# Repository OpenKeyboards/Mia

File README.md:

# Mia
122 key keyboard PCB with usb spi uart i2c

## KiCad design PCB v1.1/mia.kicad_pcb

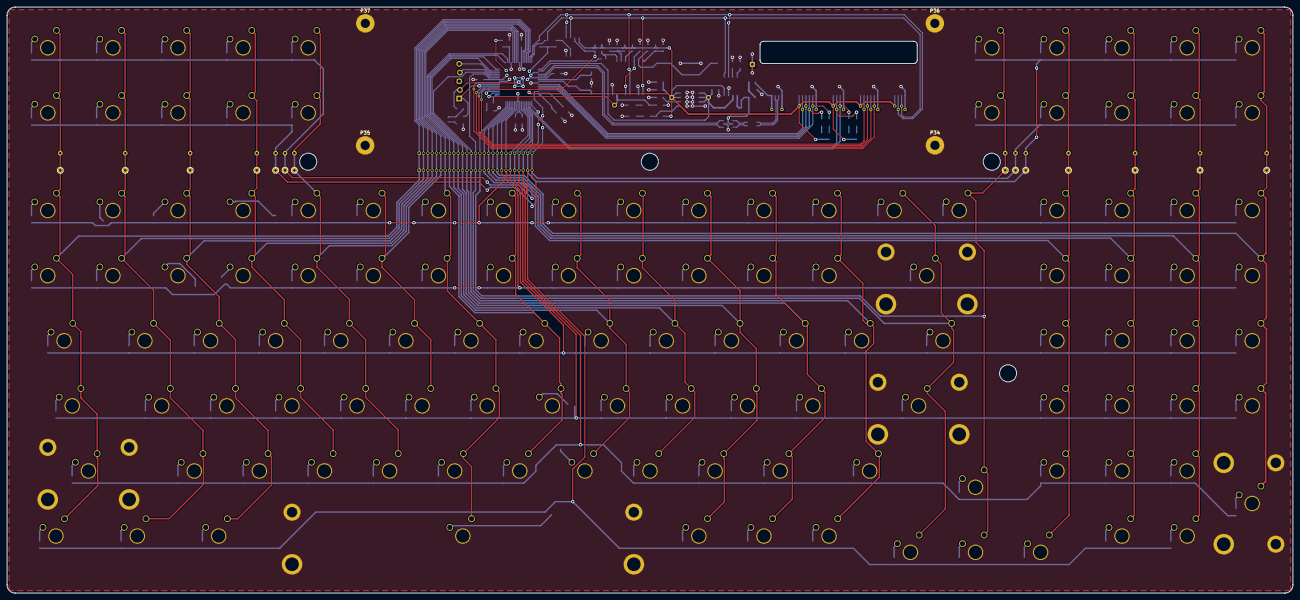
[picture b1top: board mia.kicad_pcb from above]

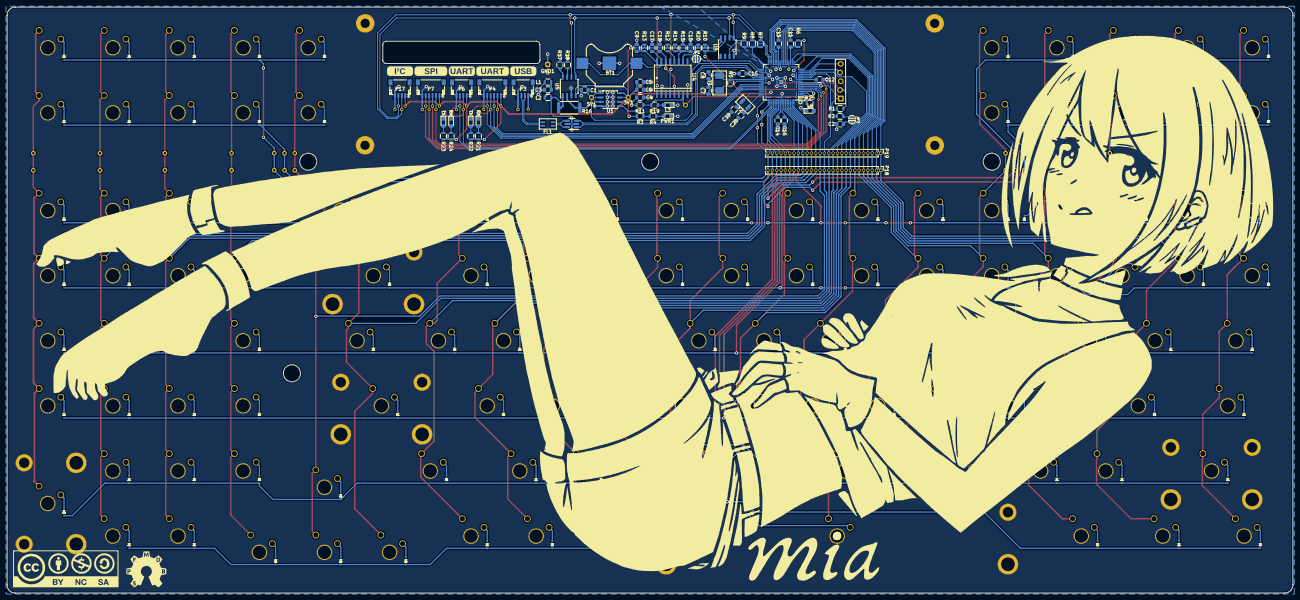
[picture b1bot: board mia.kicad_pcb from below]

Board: 2 copper layers, 376.2 x 171.5 mm, 353 parts (199 on the bottom side), 205 nets.

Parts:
3V3: 3.3V; Measurement_Point_Round-TH_Small
5V1: 5V; Measurement_Point_Round-TH_Small
BT1: Battery_Cell; Keystone_3000_1x12mm-CoinCell
C1, C5: 2.2uF; C_0805
C2, C4, C6, C9, C10, C11, C12, C13, C15, C16, C17, C18: 0.1uF; C_0805
C3: 630nF 16V; C_0805
C7, C8: 18pF; C_0805
C14: 10uF; C_0805
C19, C20: 12.5pF; C_0805
D1, D2, D3, D4, D5, D6, D7, D8, D9, D10, D11, D12, D13, D14, D15, D16, D17, D18, D19, D20, D21, D22, D23, D24, D25, D26, D27, D28, D29, D30, D31, D32, D33, D34, D35, D36, D37, D38, D39, D40, D41, D42, D43, D44, D45, D46, D47, D48, D49, D50, D51, D52, D53, D54, D55, D56, D57, D58, D59, D60, D61, D62, D63, D64, D65, D66, D67, D68, D69, D70, D71, D72, D73, D74, D75, D76, D77, D78, D79, D80, D81, D82, D83, D84, D85, D86, D87, D88, D89, D90, D91, D92, D93, D94, D95, D96, D97, D98, D99, D100, D101, D102, D103, D104, D105, D106, D107, D108, D109, D110, D111, D112, D113, D114, D116, D117, D118, D119, D120, D121, D122: D; D_SOD-323-NOMASK
D127: TVSDiodeArray; SOT-23-6_Handsoldering
FL1: EMI_Filter_LL; USBChoke
GND1: GND; Measurement_Point_Square-TH_Small
JP1, JP3: Jumper_NO_Small; SOLDER-JUMPER_1-WAY
L1, L2: 1.5A 600Ohms@100Mhz; L_0805
L3: PPS; LED_0805
L8: BL; LED_0805
P1, P8, P9, P10, P11, P12, P13, P14, P15, P16: CONN_01X01; PCBSTAB
P2: ISCP HEADER; ISCP_Header
P3: CONN_01X06; JST4x1.00mm_AngledUSB
P4, P7: CONN_01X06; JST_SH_6x1_Angled
P5: ViaPattern; spiheader
P6, P17: CONN_01X04; JST4x1.00mm_Angled
P18, P19: CONN_01X27; Pin_Header_Straight_1x27_Pitch1.27mm
P20, P21, P22, P23, P24, P25, P26, P27, P28, P29, P30, P31, P32, P33: CONN_01X01; throughholelink
P34, P35, P36, P37: CONN_01X01; MountingHole_2.7mm_M2.5_Pad
P38, P39, P40, P41: CONN_01X01; m25MountingClearance
PWR1: PWR; LED_0805
R1, R11, R12, R14, R15, R17, R18, R20: 10k; R_0805
R2: 1k; R_0805
R3: 200k; R_0805
R4: R; R_0805
R5: 1M; R_0805
R6: 10R; R_0805
R7, R8: 4.7k; R_0805
R9, R10: 100k; R_0805
R13, R19, R21, R22, R23, R24, R25: 330R; R_0805
R16: SENSE; R_2512
RX: RX; LED_0805
RX#2: RX; LED_0805
S1, S2, S3, S4, S5, S6, S7, S8, S9, S10, S11, S12, S13, S14, S15, S16, S17, S18, S19, S20, S21, S22, S23, S24, S25, S26, S27, S28, S29, S30, S31, S32, S33, S34, S35, S36, S37, S38, S39, S40, S41, S42, S43, S44, S45, S46, S47, S48, S49, S50, S51, S52, S53, S54, S55, S56, S57, S58, S59, S60, S61, S62, S63, S64, S65, S66, S67, S68, S69, S70, S71, S72, S73, S74, S75, S76, S77, S78, S79, S80, S81, S82, S83, S84, S85, S86, S87, S88, S89, S90, S91, S92, S93, S94, S95, S96, S97, S98, S99, S100, S101, S102, S103, S104, S105, S106, S107, S108, S109, S110, S111, S112, S113, S114, S116, S117, S118, S119, S120, S121, S122: SW; SW_SOCKET_COMBINED_T
TP1: TEST; Measurement_Point_Round-TH_Small
TX: TX; LED_0805
TX#2: TX; LED_0805
U1: MCP1727; SOIC-8_3.9x4.9mm_Pitch1.27mm
U2: PIC32MX470F512H
U3: M24M02-DR; SOIC-8_3.9x4.9mm_Pitch1.27mm
U4: pcf2127t; NXP-SO16
U5: INA219; SOIC-8_3.9x4.9mm_Pitch1.27mm
Y1: 20Mhz; OSCAB7
Y2: 32.768Mhz; ECX-327-CDX-1293

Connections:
+3V3: 3V3.1, C5.1, C6.1, C12.1, C13.1, C15.2, C16.1, P2.2, P4.1, P6.1, P7.1, P17.1, R1.2, R3.1, R6.2, R7.2, R8.2, R9.1, R10.2, R11.2, R12.1, R13.1, R14.1, R20.2, R21.1, R22.1, R23.1, R24.1, U1.7, U1.8, U2.10, U2.26, U2.35, U2.38, U2.57, U3.8, U5.4
+5V: 5V1.1, C1.1, R16.2, U1.1, U1.2, U1.3, U2.34, U5.2
/1D+: D127.6, FL1.2
/1D-: D127.4, FL1.3
/2D+: FL1.1, P3.3
/2D-: FL1.4, P3.2
BBS: C18.1, U4.5, U4.14
COL00: P18.1, P19.1, P20.1, S1.2, S2.2, S3.2, S4.2, S5.2, S6.2, S7.2, S8.2, U2.30
COL01: P18.2, P19.2, P21.1, S9.2, S10.2, S11.2, S12.2, S13.2, S14.2, S15.2, S16.2, U2.29
COL02: P18.3, P19.3, P22.1, S17.2, S18.2, S19.2, S20.2, S21.2, S22.2, S23.2, S24.2, U2.28
COL03: P18.4, P19.4, P23.1, S25.2, S26.2, S27.2, S28.2, S29.2, S30.2, S31.2, U2.27
COL04: P18.5, P19.5, P24.1, S32.2, S33.2, S34.2, S35.2, S36.2, S37.2, S38.2, U2.24
COL05: P18.6, P19.6, S39.2, S40.2, S41.2, S42.2, U2.23
COL06: P18.7, P19.7, S43.2, S44.2, S45.2, S46.2, S47.2, S48.2, U2.22
COL07: P18.8, P19.8, S49.2, S50.2, S51.2, S52.2, S53.2, U2.21
COL08: P18.9, P19.9, S54.2, S55.2, S56.2, S57.2, S58.2, U2.18
COL09: P18.10, P19.10, S59.2, S60.2, S61.2, S62.2, S63.2, U2.17
COL10: P18.11, P19.11, S64.2, S65.2, S66.2, S67.2, S68.2, S69.2, U2.16
COL11: P18.12, P19.12, S70.2, S71.2, S72.2, S73.2, S74.2, S75.2, U2.15
COL12: P18.13, P19.13, S76.2, S77.2, S78.2, S79.2, S80.2, U2.12
COL13: P18.14, P19.14, S81.2, S82.2, S83.2, S84.2, S85.2, U2.11
COL14: P18.15, P19.15, P25.1, S86.2, S87.2, S88.2, S89.2, S90.2, U2.64
COL15: P18.16, P19.16, P26.1, S91.2, S92.2, S93.2, S94.2, S95.2, S96.2, S97.2, S98.2, U2.63
COL16: P18.17, P19.17, P27.1, S99.2, S100.2, S101.2, S102.2, S103.2, S104.2, S105.2, S106.2, U2.62
COL17: P18.18, P19.18, P28.1, S107.2, S108.2, S109.2, S110.2, S111.2, S112.2, S113.2, S114.2, U2.61
COL18: P18.19, P19.19, P29.1, S116.2, S117.2, S118.2, S119.2, S120.2, S121.2, S122.2, U2.60
EEPROM_WRITE_CONTROL: R10.1, U2.3, U3.7
GND: BT1.2, C1.2, C2.2, C3.2, C4.2, C5.2, C6.2, C7.2, C8.2, C9.2, C10.2, C11.2, C12.2, C13.2, C14.2, C15.1, C16.2, C17.2, C18.2, C19.2, C20.2, D127.2, GND1.1, L3.1, L8.1, P1.1, P2.3, P3.4, P4.6, P6.4, P7.6, P8.1, P9.1, P10.1, P11.1, P12.1, P13.1, P14.1, P15.1, P16.1, P17.4, P34.1, P35.1, P36.1, P37.1, PWR1.1, R15.1, R17.1, R18.1, S1.3, S2.3, S3.3, S4.3, S5.3, S6.3, S7.3, S8.3, S9.3, S10.3, S11.3, S12.3, S13.3, S14.3, S15.3, S16.3, S17.3, S18.3, S19.3, S20.3, S21.3, S22.3, S23.3, S24.3, S25.3, S26.3, S27.3, S28.3, S29.3, S30.3, S31.3, S32.3, S33.3, S34.3, S35.3, S36.3, S37.3, S38.3, S39.3, S40.3, S41.3, S42.3, S43.3, S44.3, S45.3, S46.3, S47.3, S48.3, S49.3, S50.3, S51.3, S52.3, S53.3, S54.3, S55.3, S56.3, S57.3, S58.3, S59.3, S60.3, S61.3, S62.3, S63.3, S64.3, S65.3, S66.3, S67.3, S68.3, S69.3, S70.3, S71.3, S72.3, S73.3, S74.3, S75.3, S76.3, S77.3, S78.3, S79.3, S80.3, S81.3, S82.3, S83.3, S84.3, S85.3, S86.3, S87.3, S88.3, S89.3, S90.3, S91.3, S92.3, S93.3, S94.3, S95.3, S96.3, S97.3, S98.3, S99.3, S100.3, S101.3, S102.3, S103.3, S104.3, S105.3, S106.3, S107.3, S108.3, S109.3, S110.3, S111.3, S112.3, S113.3, S114.3, S116.3, S117.3, S118.3, S119.3, S120.3, S121.3, S122.3, U1.4, U2.9, U2.20, U2.25, U2.41, U3.4, U4.2, U4.8, U5.3
MCLR: P2.1, R2.1, U2.7
unnamed: BT1.1, C17.1, U4.15
unnamed: C2.1, JP3.2
unnamed: C3.1, L1.1, L2.2
unnamed: C4.1, U1.6
unnamed: C9.1, R13.2, U4.16
unnamed: C10.1, R14.2, R15.2, U4.11
unnamed: C11.1, R6.1, U2.19
unnamed: C14.1, U2.56
unnamed: D1.1, S1.1
unnamed: D2.1, S2.1
unnamed: D3.1, S3.1
unnamed: D4.1, S4.1
unnamed: D5.1, S5.1
unnamed: D6.1, S6.1
unnamed: D7.1, S7.1
unnamed: D8.1, S8.1
unnamed: D9.1, S9.1
unnamed: D10.1, S10.1
unnamed: D11.1, S11.1
unnamed: D12.1, S12.1
unnamed: D13.1, S13.1
unnamed: D14.1, S14.1
unnamed: D15.1, S15.1
unnamed: D16.1, S16.1
unnamed: D17.1, S17.1
unnamed: D18.1, S18.1
unnamed: D19.1, S19.1
unnamed: D20.1, S20.1
unnamed: D21.1, S21.1
unnamed: D22.1, S22.1
unnamed: D23.1, S23.1
unnamed: D24.1, S24.1
unnamed: D25.1, S25.1
unnamed: D26.1, S26.1
unnamed: D27.1, S27.1
unnamed: D28.1, S28.1
unnamed: D29.1, S29.1
unnamed: D30.1, S30.1
unnamed: D31.1, S31.1
unnamed: D32.1, S32.1
unnamed: D33.1, S33.1
unnamed: D34.1, S34.1
unnamed: D35.1, S35.1
unnamed: D36.1, S36.1
unnamed: D37.1, S37.1
unnamed: D38.1, S38.1
unnamed: D39.1, S39.1
unnamed: D40.1, S40.1
unnamed: D41.1, S41.1
unnamed: D42.1, S42.1
unnamed: D43.1, S43.1
unnamed: D44.1, S44.1
unnamed: D45.1, S45.1
unnamed: D46.1, S46.1
unnamed: D47.1, S47.1
unnamed: D48.1, S48.1
unnamed: D49.1, S49.1
unnamed: D50.1, S50.1
unnamed: D51.1, S51.1
unnamed: D52.1, S52.1
unnamed: D53.1, S53.1
unnamed: D54.1, S54.1
unnamed: D55.1, S55.1
unnamed: D56.1, S56.1
unnamed: D57.1, S57.1
unnamed: D58.1, S58.1
unnamed: D59.1, S59.1
unnamed: D60.1, S60.1
unnamed: D61.1, S61.1
unnamed: D62.1, S62.1
unnamed: D63.1, S63.1
unnamed: D64.1, S64.1
unnamed: D65.1, S65.1
unnamed: D66.1, S66.1
unnamed: D67.1, S67.1
unnamed: D68.1, S68.1
unnamed: D69.1, S69.1
unnamed: D70.1, S70.1
unnamed: D71.1, S71.1
unnamed: D72.1, S72.1
unnamed: D73.1, S73.1
unnamed: D74.1, S74.1
unnamed: D75.1, S75.1
unnamed: D76.1, S76.1
unnamed: D77.1, S77.1
unnamed: D78.1, S78.1
unnamed: D79.1, S79.1
unnamed: D80.1, S80.1
unnamed: D81.1, S81.1
unnamed: D82.1, S82.1
unnamed: D83.1, S83.1
unnamed: D84.1, S84.1
unnamed: D85.1, S85.1
unnamed: D86.1, S86.1
unnamed: D87.1, S87.1
unnamed: D88.1, S88.1
unnamed: D89.1, S89.1
unnamed: D90.1, S90.1
unnamed: D91.1, S91.1
unnamed: D92.1, S92.1
unnamed: D93.1, S93.1
unnamed: D94.1, S94.1
unnamed: D95.1, S95.1
unnamed: D96.1, S96.1
unnamed: D97.1, S97.1
unnamed: D98.1, S98.1
unnamed: D99.1, S99.1
unnamed: D100.1, S100.1
unnamed: D101.1, S101.1
unnamed: D102.1, S102.1
unnamed: D103.1, S103.1
unnamed: D104.1, S104.1
unnamed: D105.1, S105.1
unnamed: D106.1, S106.1
unnamed: D107.1, S107.1
unnamed: D108.1, S108.1
unnamed: D109.1, S109.1
unnamed: D110.1, S110.1
unnamed: D111.1, S111.1
unnamed: D112.1, S112.1
unnamed: D113.1, S113.1
unnamed: D114.1, S114.1
unnamed: D116.1, S116.1
unnamed: D117.1, S117.1
unnamed: D118.1, S118.1
unnamed: D119.1, S119.1
unnamed: D120.1, S120.1
unnamed: D121.1, S121.1
unnamed: D122.1, S122.1
unnamed: D127.5, L2.1, R16.1, U5.1
unnamed: JP1.2, R20.1, U4.10
unnamed: JP3.1, R1.1, R2.2
unnamed: L1.2, P3.1
unnamed: L3.2, R19.2
unnamed: R21.2, RX.2
unnamed: R22.2, TX.2
unnamed: R23.2, TX#2.2
unnamed: R24.2, RX#2.2
unnamed: L8.2, R25.2
unnamed: PWR1.2, R4.1
unnamed: R3.2, R4.2, U1.5
unnamed: R9.2, U3.3
unnamed: R12.2, U4.12
unnamed: R17.2, U5.8
unnamed: R18.2, U5.7
unnamed: R25.1, U2.1
OSC1: C8.1, R5.2, U2.39, Y1.1
OSC2: C7.1, R5.1, U2.40, Y1.2
PGEC3: P2.5, U2.14
PGED3: P2.4, U2.13
POWERFAIL: JP1.1, U2.33
ROW0: D1.2, D9.2, D17.2, D25.2, D32.2, D86.2, D91.2, D99.2, D107.2, D116.2, P18.26, P19.26, P30.1, P32.1, U2.49
ROW1: D2.2, D10.2, D18.2, D26.2, D33.2, D87.2, D92.2, D100.2, D108.2, D117.2, P18.27, P19.27, P31.1, P33.1, U2.46
ROW2: D3.2, D11.2, D19.2, D27.2, D34.2, D39.2, D43.2, D49.2, D54.2, D59.2, D64.2, D70.2, D76.2, D81.2, D88.2, D93.2, D101.2, D109.2, D118.2, P18.20, P19.20, U2.59
ROW3: D4.2, D12.2, D20.2, D28.2, D35.2, D40.2, D44.2, D50.2, D55.2, D60.2, D65.2, D71.2, D77.2, D82.2, D94.2, D102.2, D110.2, D119.2, P18.21, P19.21, U2.58
ROW4: D5.2, D13.2, D21.2, D29.2, D36.2, D41.2, D45.2, D51.2, D56.2, D61.2, D66.2, D72.2, D78.2, D83.2, D95.2, D103.2, D111.2, D120.2, P18.22, P19.22, U2.55
ROW5: D6.2, D14.2, D22.2, D30.2, D37.2, D42.2, D46.2, D52.2, D57.2, D62.2, D67.2, D73.2, D84.2, D96.2, D104.2, D112.2, D121.2, P18.23, P19.23, U2.54
ROW6: D7.2, D15.2, D23.2, D31.2, D38.2, D47.2, D53.2, D58.2, D63.2, D68.2, D74.2, D79.2, D89.2, D97.2, D105.2, D113.2, D122.2, P18.24, P19.24, U2.53
ROW7: D8.2, D16.2, D24.2, D48.2, D69.2, D75.2, D80.2, D85.2, D90.2, D98.2, D106.2, D114.2, P18.25, P19.25, U2.52
RTC_CLK: R11.1, R19.1, TP1.1, U2.2, U4.7
SCL2: P17.3, R8.1, U2.32, U3.6, U4.1, U5.5
SDA2: P17.2, R7.1, U2.31, U3.5, U4.4, U5.6
SOSCI: C19.1, U2.47, Y2.2
SOSCO: C20.1, U2.48, Y2.1
SPI2-CLK: P5.1, P7.2, U2.4
SPI2-CS: P5.4, P7.5, U2.8
SPI2-MISO: P5.2, P7.3, U2.5
SPI2-MOSI: P5.3, P7.4, U2.6
UART1CTS: P4.3, U2.43
UART1RTS: P4.2, U2.42
UART1RX: P4.4, RX.1, U2.44
UART1TX: P4.5, TX.1, U2.45
UART3RX: P6.3, RX#2.1, U2.51
UART3TX: P6.2, TX#2.1, U2.50
USB0_D+: D127.1, U2.37
USB0_D-: D127.3, U2.36

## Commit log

2018-04-07 initial prototype
